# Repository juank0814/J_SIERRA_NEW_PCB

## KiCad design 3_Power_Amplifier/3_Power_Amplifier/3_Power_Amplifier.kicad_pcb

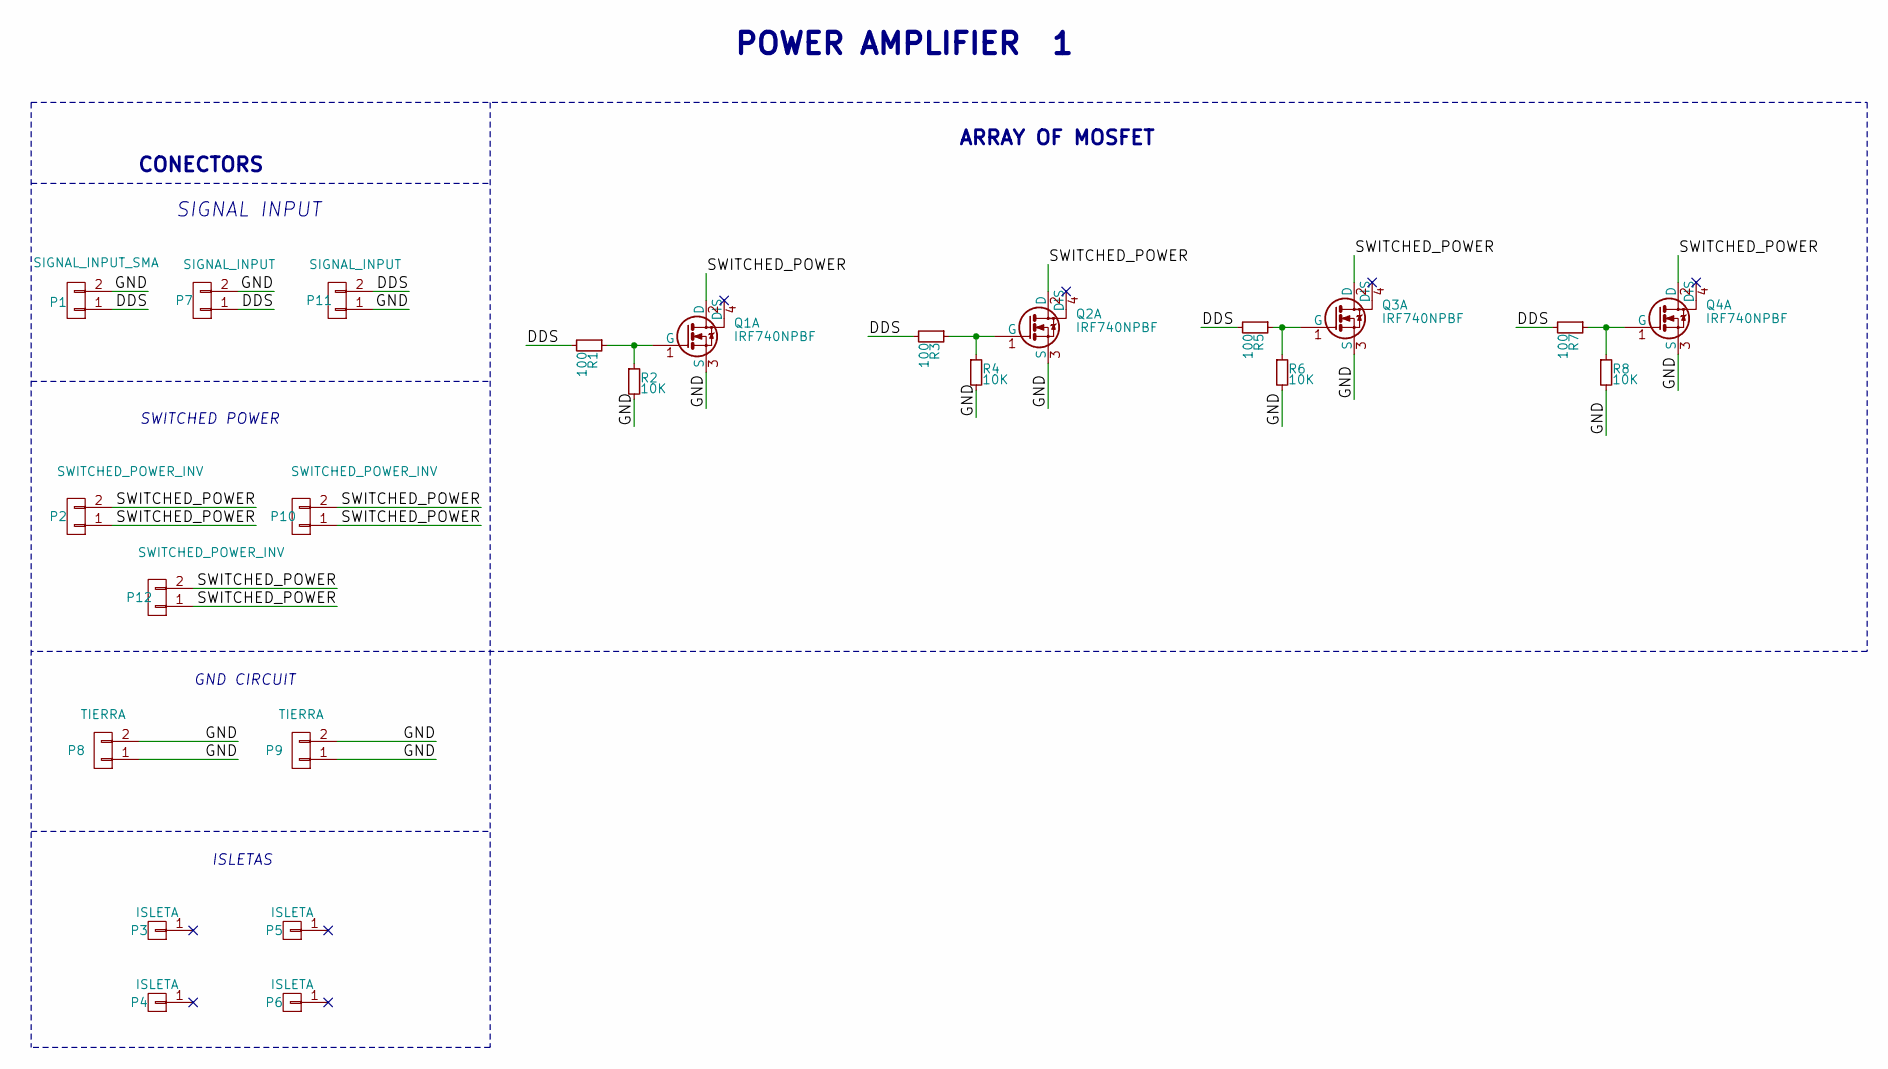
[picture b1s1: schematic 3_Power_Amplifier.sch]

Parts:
P1: SIGNAL_INPUT_SMA; INV_SMA_THT_Jack_Straight
P2, P10, P12: SWITCHED_POWER_INV; INV_Socket_MOLEX-2-pines
P3, P4, P5, P6: ISLETA; MountingHole_3.2mm_M3_Pad_Via
P7, P11: SIGNAL_INPUT; REDISEÑADO_INV_Pin_Header_Pitch2.54mm
P8, P9: TIERRA; INV_Socket_MOLEX-2-pines
Q1, Q2, Q3, Q4: IRF740NPBF; TO-220_Ver_Disipador
R1, R3, R5, R7: 100; R_0805_HandSoldering
R2, R4, R6, R8: 10K; R_0805_HandSoldering

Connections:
/DDS: P1.1, P7.1, P11.2, R1.2, R3.2, R5.2, R7.2
/GND: P1.2, P7.2, P8.1, P8.2, P9.1, P9.2, P11.1, Q1.3 (S), Q2.3 (S), Q3.3 (S), Q4.3 (S), R2.2, R4.2, R6.2, R8.2
/SWITCHED_POWER: P2.1, P2.2, P10.1, P10.2, P12.1, P12.2, Q1.2 (D), Q2.2 (D), Q3.2 (D), Q4.2 (D)
unnamed: Q1.1 (G), R1.1, R2.1
unnamed: Q2.1 (G), R3.1, R4.1
unnamed: Q3.1 (G), R5.1, R6.1
unnamed: Q4.1 (G), R7.1, R8.1

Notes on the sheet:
CONECTORS
ARRAY OF MOSFET
POWER AMPLIFIER 1
SIGNAL INPUT
SWITCHED POWER
GND CIRCUIT
ISLETAS

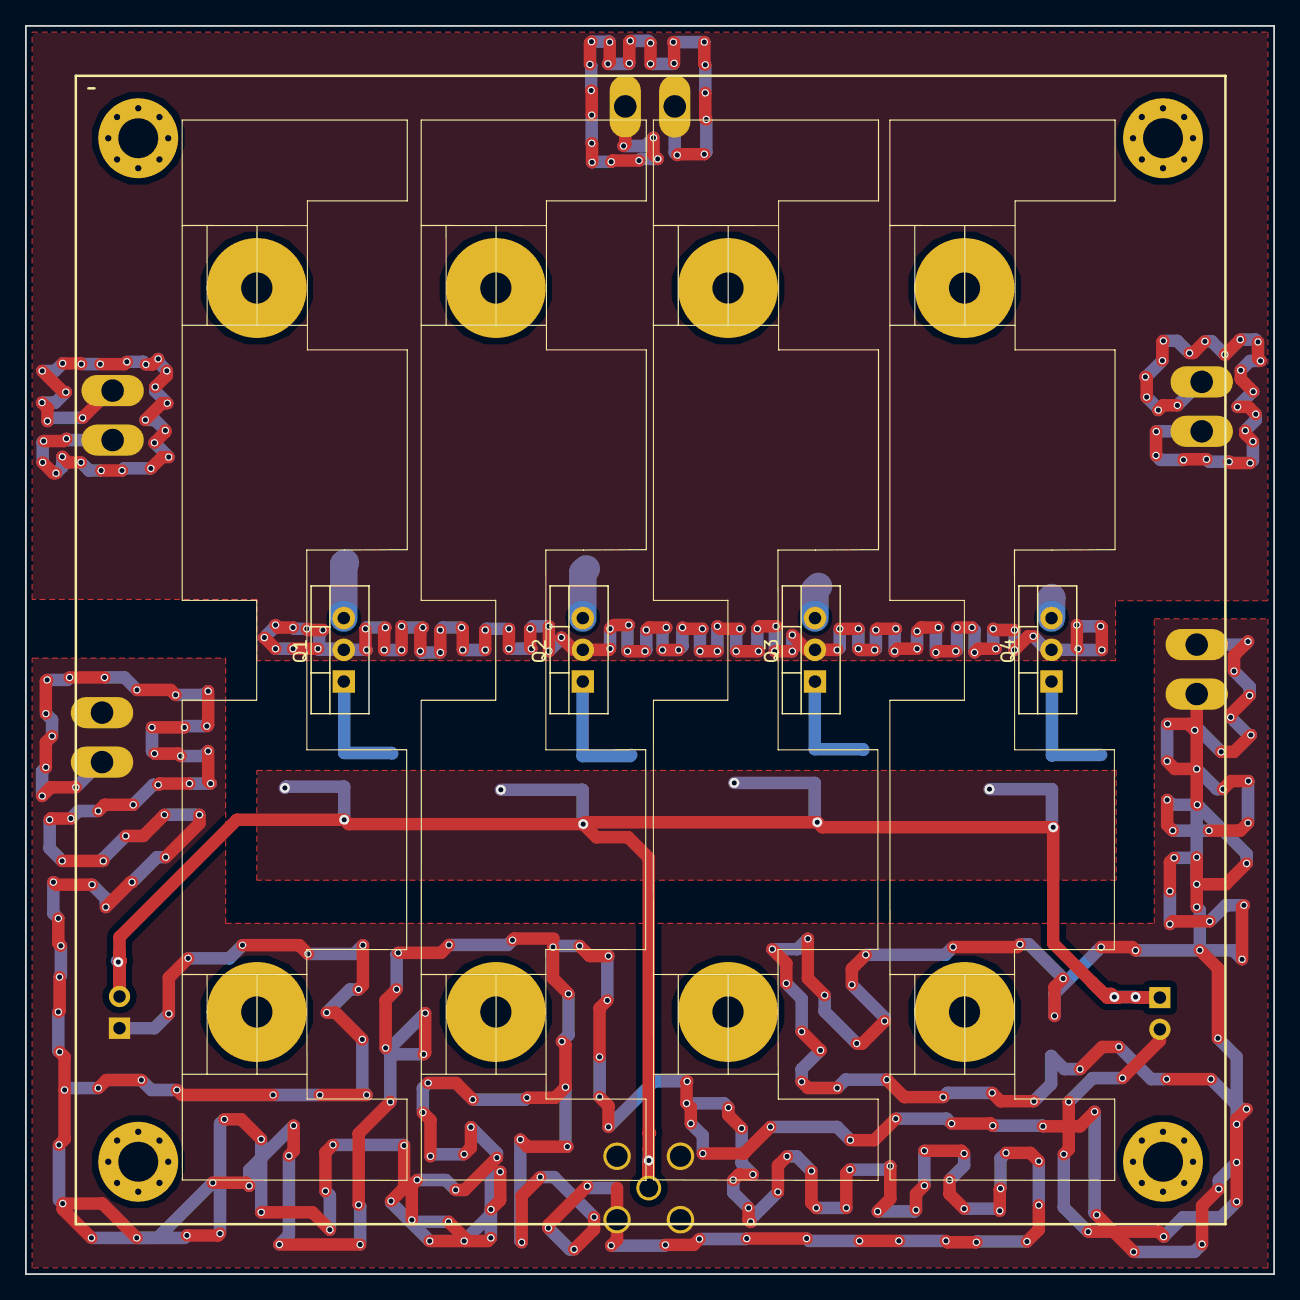
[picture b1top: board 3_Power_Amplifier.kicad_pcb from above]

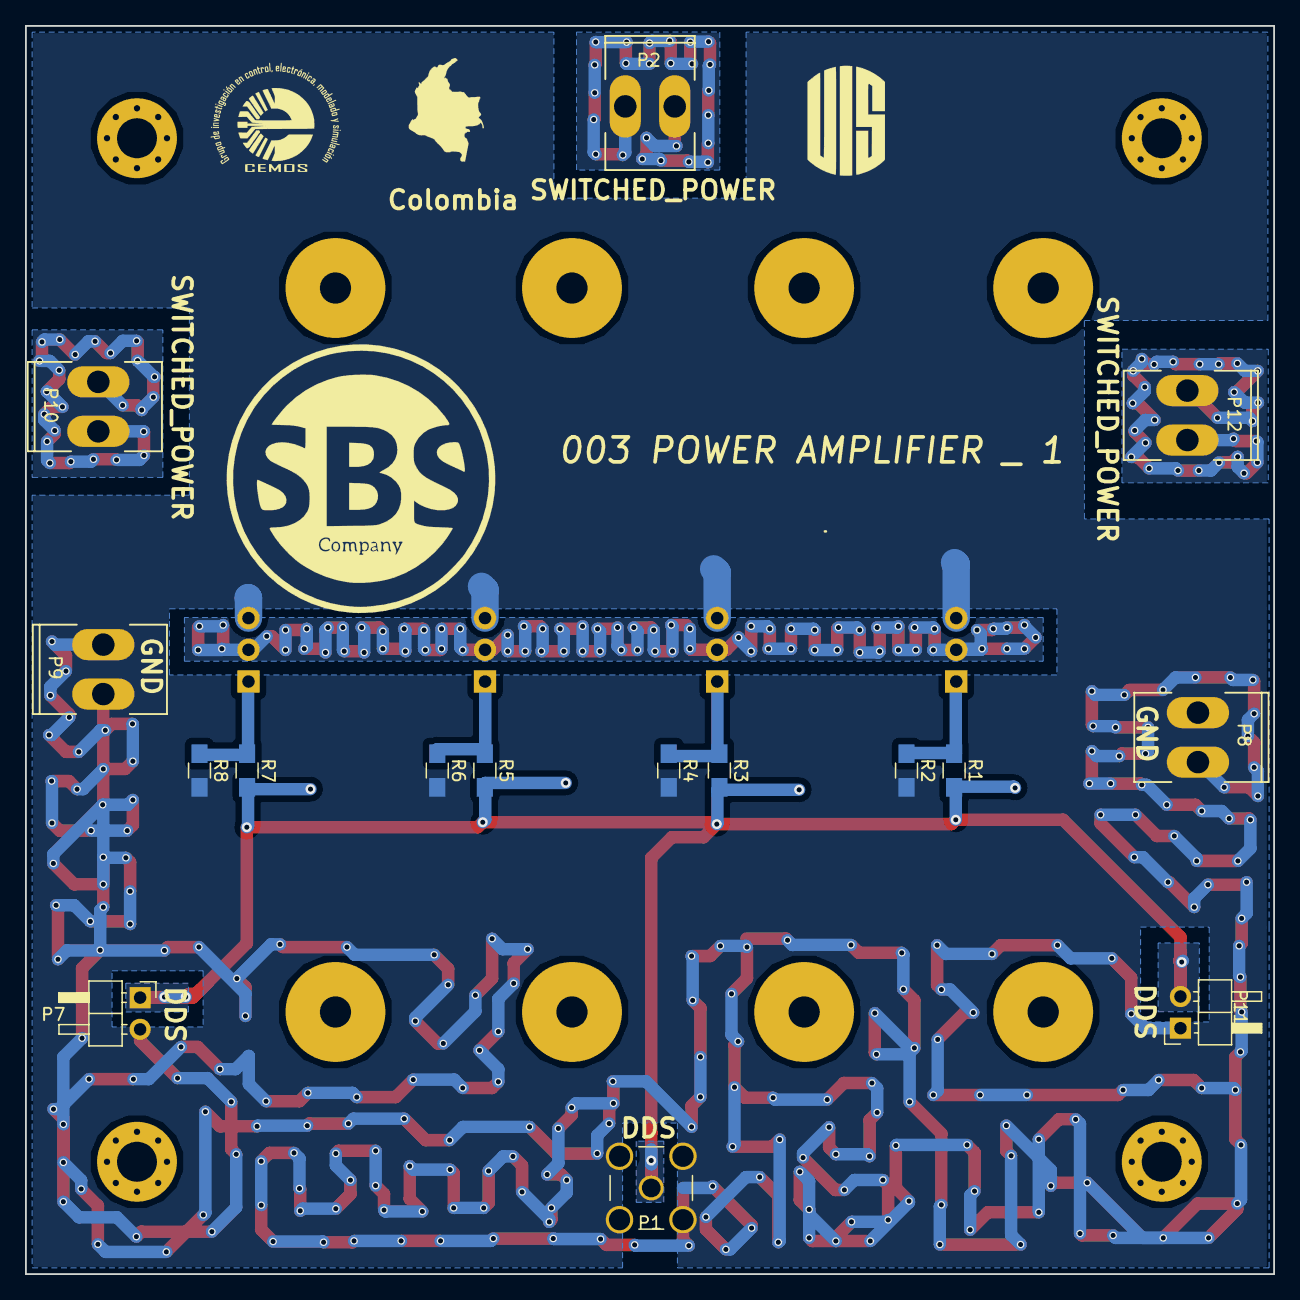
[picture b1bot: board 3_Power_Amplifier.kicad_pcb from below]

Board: 2 copper layers, 100.0 x 100.0 mm, 24 parts (8 on the bottom side), 7 nets.

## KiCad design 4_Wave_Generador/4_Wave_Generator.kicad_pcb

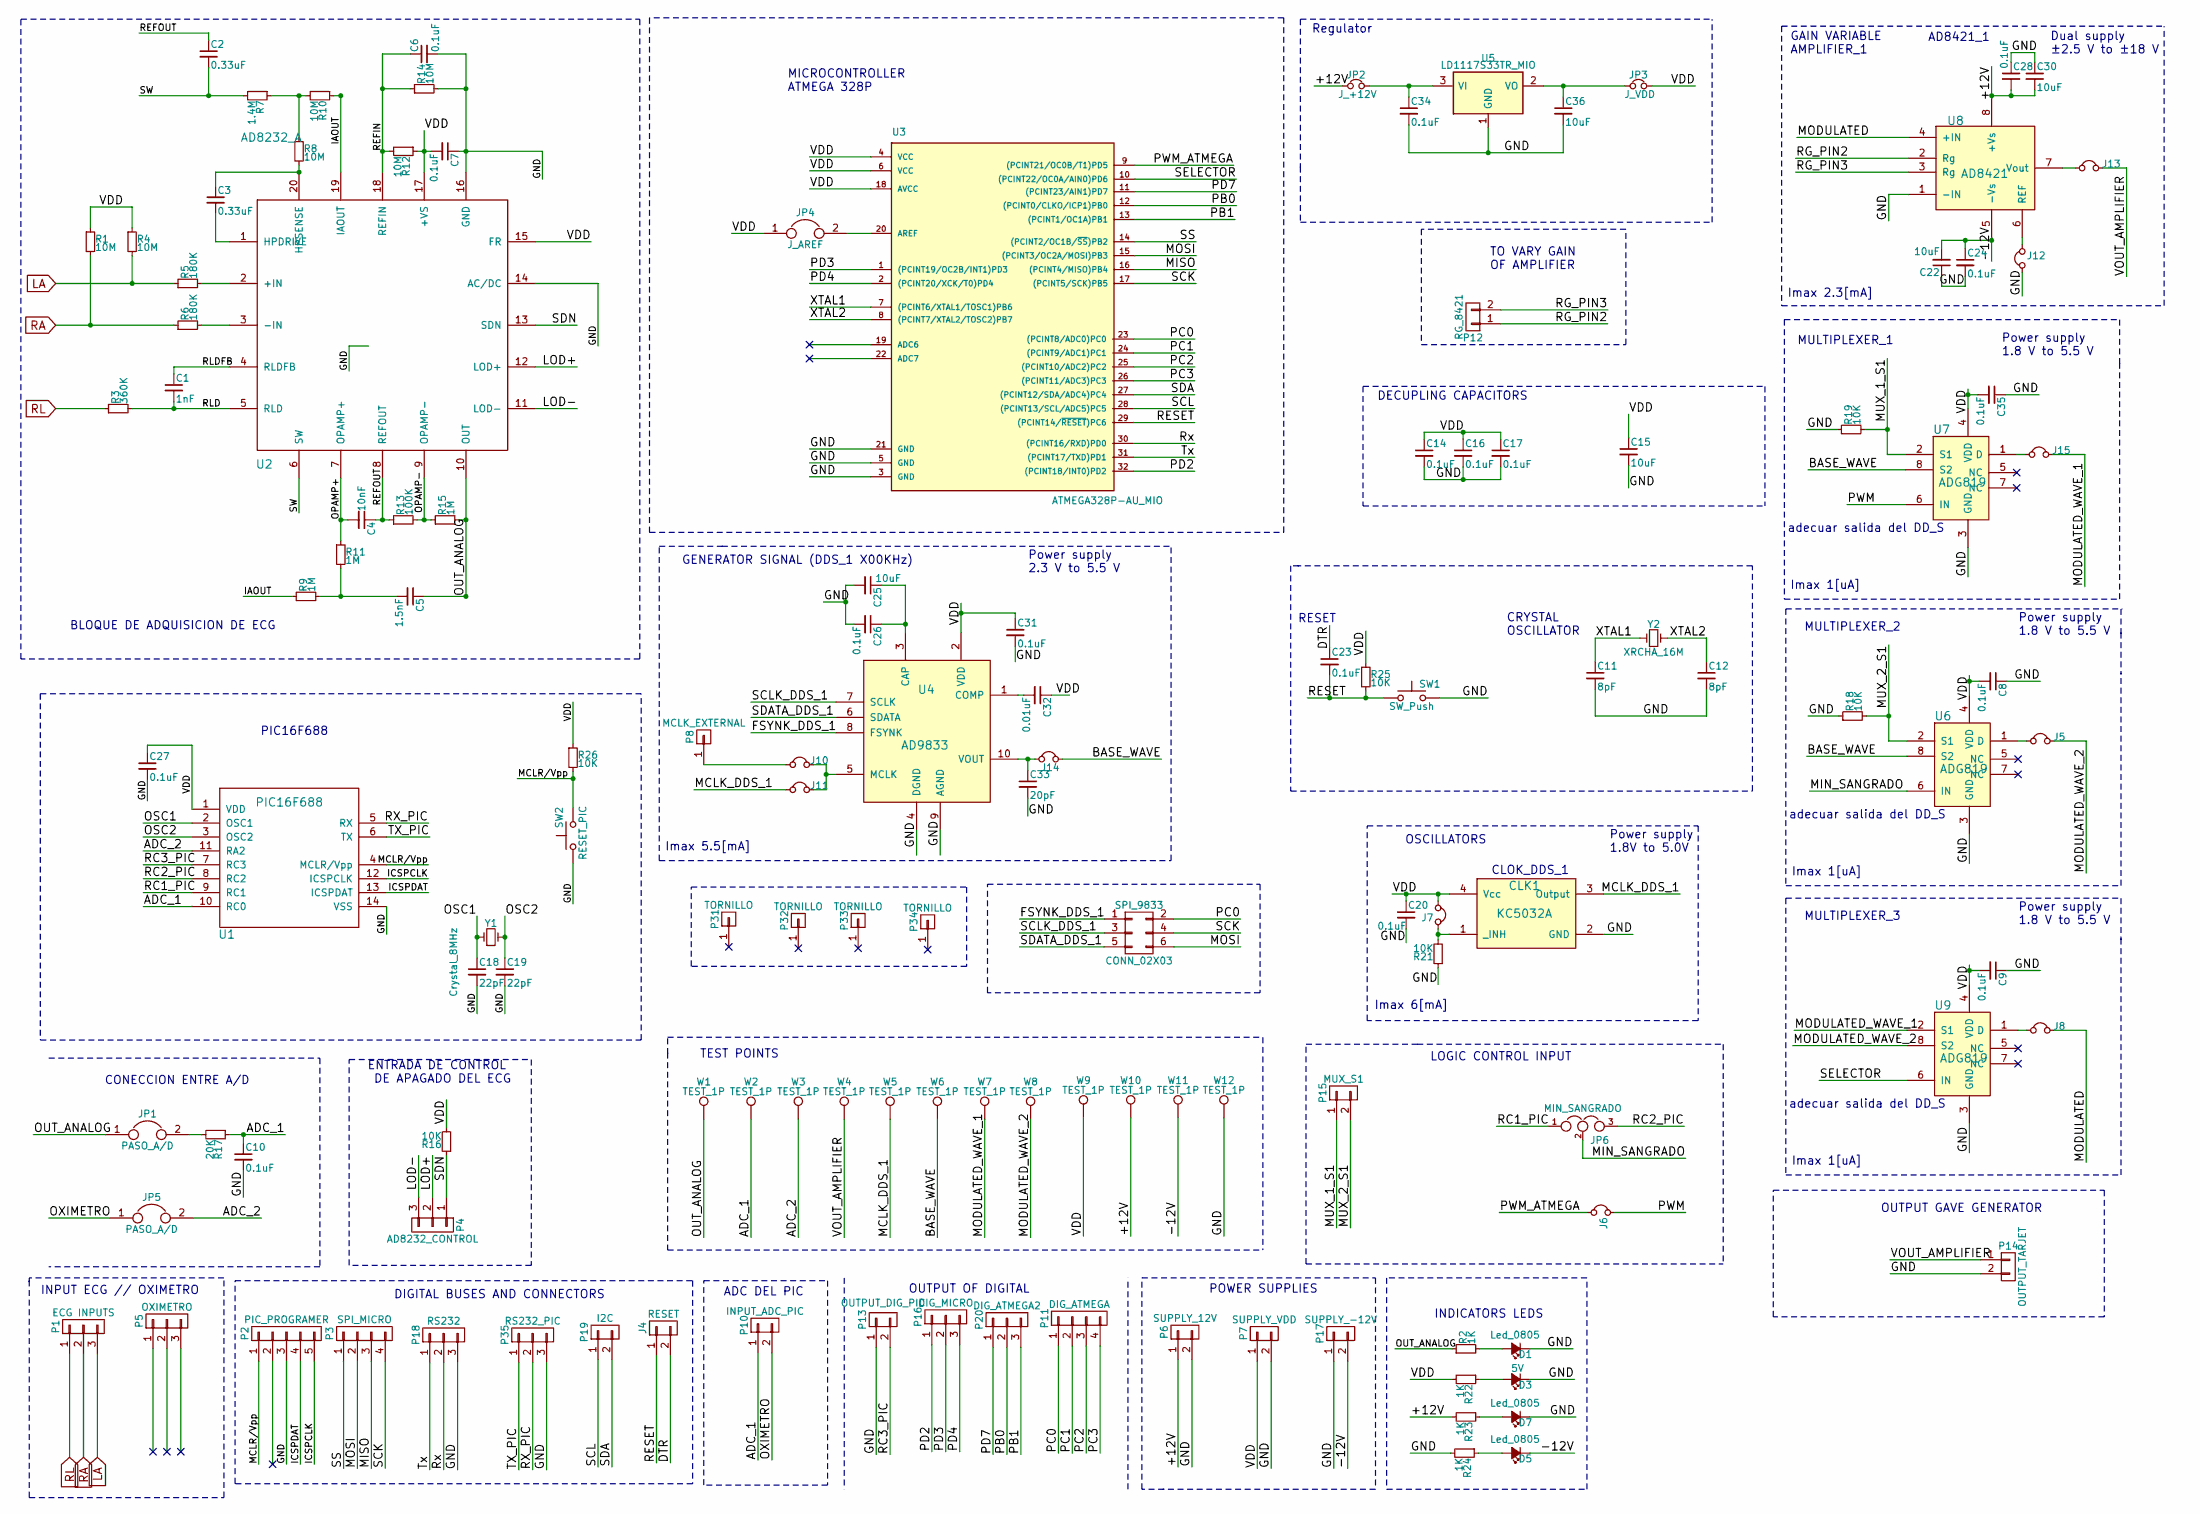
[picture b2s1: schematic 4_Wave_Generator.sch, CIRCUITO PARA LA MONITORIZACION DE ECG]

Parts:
C1: 1nF; C_0805_HandSoldering
C2, C3: 0.33uF; C_0805_HandSoldering
C4: 10nF; C_0805_HandSoldering
C5: 1.5nF; C_0805_HandSoldering
C6, C7, C10, C27: 0.1uF; C_0805_HandSoldering
C8, C9, C20, C24, C26, C28, C31, C35: 0.1uF; C_0805_HandSoldering; Digi-Key Part Number 478-1395-2-ND
C11, C12: 8pF; R_0402
C14, C16, C17, C23, C34: 0.1uF; R_0805_HandSoldering; Digi-Key Part Number 478-1395-2-ND
C15, C25: 10uF; C_0805_HandSoldering
C18, C19: 22pF; C_0805_HandSoldering
C22, C30: 10uF; C_1206_HandSoldering
C32: 0.01uF; C_0805_HandSoldering; Digi-Key Part Number 478-1383-2-ND
C33: 20pF; C_0805_HandSoldering
C36: 10uF; R_0805_HandSoldering
CLK1: KC5032A; KC5032A_Foot_Print
D1, D5, D7: Led_0805; R_0805_HandSoldering; Digi-Key Part Number 475-1410-2-ND
D3: 5V; R_0805_HandSoldering; Digi-Key Part Number 475-1410-2-ND
J4: RESET; RESET_CONNECTOR
J5, J6, J7, J8, J10, J11, J12, J13, J14, J15: Jumper; Pin_Header_Straight_1x02_Pitch2.54mm
JP1, JP5: PASO_A/D; Pin_Header_Straight_1x02_Pitch2.54mm
JP2: J_+12V; Pin_Header_Straight_1x02_Pitch2.54mm
JP3: J_VDD; Pin_Header_Straight_1x02_Pitch2.54mm
JP4: J_AREF; Pin_Header_Straight_1x02_Pitch2.54mm
JP6: MIN_SANGRADO; Pin_Header_Straight_1x03_Pitch2.54mm
P1: ECG INPUTS; Pin_Header_Straight_1x03_Pitch2.54mm
P2: PIC_PROGRAMER
P3: SPI_MICRO; SPI_CONNECTOR
P4: AD8232_CONTROL; Pin_Header_Straight_1x03_Pitch2.54mm
P5: OXIMETRO
P6: SUPPLY_12V
P7: SUPPLY_VDD; SUPPLY_5V
P8: MCLK_EXTERNAL
P10: INPUT_ADC_PIC; ADC_PIC
P11: DIG_ATMEGA; Pin_Header_Straight_1x04_Pitch2.54mm
P12: RG_8421
P13: OUTPUT_DIG_PIC; Pin_Header_Straight_1x02_Pitch2.54mm
P14: OUTPUT_TARJET; VOUT
P15: MUX_S1; Pin_Header_Straight_1x02_Pitch2.54mm
P16: DIG_MICRO; Pin_Header_Straight_1x03_Pitch2.54mm
P17: SUPPLY_-12V
P18: RS232
P19: I2C; I2C_2X4
P20: DIG_ATMEGA2; Pin_Header_Straight_1x03_Pitch2.54mm
P31, P32, P33, P34: TORNILLO; MountingHole_3.2mm_M3_Pad_Via
P35: RS232_PIC; RS232
R1, R4, R8, R10, R12, R14: 10M; R_0805_HandSoldering
R2, R22, R23, R24: 1K; R_0805_HandSoldering
R3: 360K; R_0805_HandSoldering
R5, R6: 180K; R_0805_HandSoldering
R7: 1.4M; R_0805_HandSoldering
R9, R11, R15: 1M; R_0805_HandSoldering
R13: 100K; R_0805_HandSoldering
R16, R18, R19, R21, R25, R26: 10K; R_0805_HandSoldering
R17: 20K; R_0805_HandSoldering
SPI_9833: CONN_02X03; SPI_9833
SW1: SW_Push; KPT_1187B
SW2: RESET_PIC; KPT_1187B
U1: PIC16F688; SOIC-14_3.9x8.7mm_Pitch1.27mm
U2: AD8232_A; AD8232_ECG
U3: ATMEGA328P-AU_MIO; TQFP-32_7x7mm_Pitch0.8mm
U4: AD9833; MSOP-10_3x3mm_Pitch0.5mm
U5: LD1117S33TR_MIO; SOT-223_este
U6, U7, U9: ADG819; MSOP-8_3x3mm_Pitch0.65mm
U8: AD8421; SOIC-8_3.9x4.9mm_Pitch1.27mm
W1, W2, W3, W4, W5, W6, W7, W8, W9, W10, W11, W12: TEST_1P; Measurement_Point_Round-TH_Small
Y1: Crystal_8MHz; Crystal_SMD_Abracon_ABM3-2pin_5.0x3.2mm_HandSoldering
Y2: XRCHA_16M; Crystal_SMD_XRCHA_Murata_Serie_W2,5mm_L2,0mm

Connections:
/+12V: C28.2, C30.2, JP2.1, P6.1, R23.2, U8.8 (+Vs), W10.1; also elsewhere on the board
/-12V: C22.2, C24.1, D5.1 (K), P17.2, U8.5 (-Vs), W11.1; also elsewhere on the board
/ADC_1: C10.1, P10.1, R17.1, U1.10 (RC0), W2.1
/ADC_2: JP5.2, U1.11 (RA2), W3.1
/BASE_WAVE: J14.1, U6.8 (S2), U7.8 (S2), W6.1; also elsewhere on the board
/DTR: C23.1, J4.2
/FSYNK_DDS_1: SPI_9833.1, U4.8 (FSYNK)
/GND: C6.2, C7.1, C8.1, C9.1, C10.2, C11.2, C12.2, C14.2, C15.2, C16.2, C17.2, C18.2, C19.2, C20.2, C22.1, C24.2, C25.2, C26.2, C27.2, C28.1, C30.1, C31.2, C33.2, C34.2, C35.1, C36.2, CLK1.2 (GND), D1.1 (K), D3.1 (K), D7.1 (K), J12.2, P2.3, P6.2, P7.2, P13.1, P14.2, P17.1, P18.3, P35.3, R14.2, R18.1, R19.1, R21.1, R24.2, SW1.2, SW2.1, U1.14 (VSS), U2.14 (AC/DC), U2.16 (GND), U2.21 (GND), U3.3 (GND), U3.5 (GND), U3.21 (GND), U4.4 (DGND), U4.9 (AGND), U5.1 (GND), U6.3 (GND), U7.3 (GND), U8.1 (-IN), U9.3 (GND), W12.1; also elsewhere on the board
/IAOUT: R9.1, R10.1, U2.19 (IAOUT); also elsewhere on the board
/ICSPCLK: P2.5, U1.12 (ICSPCLK)
/ICSPDAT: P2.4, U1.13 (ICSPDAT)
/LOD+: P4.2 (LA), U2.12 (LOD+); also elsewhere on the board
/LOD-: P4.3 (RA), U2.11 (LOD-); also elsewhere on the board
/MCLK_DDS_1: CLK1.3 (Output), J11.2, W5.1
/MCLR/Vpp: P2.1, R26.2, SW2.2, U1.4 (MCLR/Vpp)
/MIN_SANGRADO: JP6.2, U6.6 (IN); also elsewhere on the board
/MISO: P3.3, U3.16 ((PCINT4/MISO)PB4)
/MODULATED: J8.1, U8.4 (+IN); also elsewhere on the board
/MODULATED_WAVE_1: J15.1, U9.2 (S1), W7.1; also elsewhere on the board
/MODULATED_WAVE_2: J5.1, U9.8 (S2), W8.1; also elsewhere on the board
/MOSI: P3.2, SPI_9833.6, U3.15 ((PCINT3/OC2A/MOSI)PB3)
/MUX_1_S1: P15.1, R19.2, U7.2 (S1); also elsewhere on the board
/MUX_2_S1: P15.2, R18.2, U6.2 (S1); also elsewhere on the board
/OPAMP+: C4.2, R11.1, U2.7 (OPAMP+); also elsewhere on the board
/OSC1: C18.1, U1.2 (OSC1), Y1.1
/OSC2: C19.1, U1.3 (OSC2), Y1.2
/OUT_ANALOG: C5.1, JP1.1, R2.1, R15.2, U2.10 (OUT), W1.1; also elsewhere on the board
/OXIMETRO: JP5.1, P10.2
/PB0: P20.2, U3.12 ((PCINT0/CLKO/ICP1)PB0)
/PB1: P20.3, U3.13 ((PCINT1/OC1A)PB1)
/PC0: P11.1, SPI_9833.2, U3.23 ((PCINT8/ADC0)PC0)
/PC1: P11.2, U3.24 ((PCINT9/ADC1)PC1)
/PC2: P11.3, U3.25 ((PCINT10/ADC2)PC2)
/PC3: P11.4, U3.26 ((PCINT11/ADC3)PC3)
/PD2: P16.1, U3.32 ((PCINT18/INT0)PD2)
/PD3: P16.2, U3.1 ((PCINT19/OC2B/INT1)PD3)
/PD4: P16.3, U3.2 ((PCINT20/XCK/T0)PD4)
/PD7: P20.1, U3.11 ((PCINT23/AIN1)PD7)
/PWM: J6.1, U7.6 (IN); also elsewhere on the board
/PWM_ATMEGA: J6.2, U3.9 ((PCINT21/OC0B/T1)PD5)
/RC1_PIC: JP6.1, U1.9 (RC1)
/RC2_PIC: JP6.3, U1.8 (RC2)
/RC3_PIC: P13.2, U1.7 (RC3)
/REFIN: C6.1, R12.2, R14.1, U2.18 (REFIN); also elsewhere on the board
/REFOUT: C2.1, C4.1, R13.1, U2.8 (REFOUT); also elsewhere on the board
/RESET: C23.2, J4.1, R25.2, SW1.1, U3.29 ((PCINT14/~RESET~)PC6)
/RG_PIN2: P12.1, U8.2 (Rg); also elsewhere on the board
/RG_PIN3: P12.2, U8.3 (Rg); also elsewhere on the board
/RLD: C1.2, R3.2, U2.5 (RLD); also elsewhere on the board
/RLDFB: C1.1, U2.4 (RLDFB); also elsewhere on the board
/RX_PIC: P35.2, U1.5 (RX)
/Rx: P18.2, U3.30 ((PCINT16/RXD)PD0)
/SCK: P3.4, SPI_9833.4, U3.17 ((PCINT5/SCK)PB5)
/SCL: P19.1, U3.28 ((PCINT13/SCL/ADC5)PC5)
/SCLK_DDS_1: SPI_9833.3, U4.7 (SCLK)
/SDA: P19.2, U3.27 ((PCINT12/SDA/ADC4)PC4)
/SDATA_DDS_1: SPI_9833.5, U4.6 (SDATA)
/SDN: P4.1 (RL), R16.1, U2.13 (SDN); also elsewhere on the board
/SELECTOR: U3.10 ((PCINT22/OC0A/AIN0)PD6), U9.6 (IN); also elsewhere on the board
/SS: P3.1, U3.14 ((PCINT2/OC1B/~SS~)PB2)
/SW: C2.2, R7.2, U2.6 (SW); also elsewhere on the board
/TX_PIC: P35.1, U1.6 (TX)
/Tx: P18.1, U3.31 ((PCINT17/TXD)PD1)
/VDD: C7.2, C8.2, C9.2, C14.1, C15.1, C16.1, C17.1, C20.1, C27.1, C31.1, C32.1, C35.2, CLK1.4 (Vcc), J7.2, JP3.2, JP4.1, P7.1, R1.1, R4.1, R12.1, R16.2, R22.2, R25.1, R26.1, U1.1 (VDD), U2.15 (FR), U2.17 (+VS), U3.4 (VCC), U3.6 (VCC), U3.18 (AVCC), U4.2 (VDD), U6.4 (VDD), U7.4 (VDD), U9.4 (VDD), W9.1; also elsewhere on the board
/VOUT_AMPLIFIER: J13.1, P14.1, W4.1
/XTAL1: C11.1, U3.7 ((PCINT6/XTAL1/TOSC1)PB6), Y2.1
/XTAL2: C12.1, U3.8 ((PCINT7/XTAL2/TOSC2)PB7), Y2.2
LA: P1.3 (RA), R4.2, R5.1
unnamed 68: C3.1, R8.2, U2.20 (HPSENSE); also elsewhere on the board
unnamed 69: C3.2, U2.1 (HPDRIVE); also elsewhere on the board
unnamed: C5.2, R9.2, R11.2
unnamed: C25.1, C26.1, U4.3 (CAP)
unnamed: C32.2, U4.1 (COMP)
unnamed: C33.1, J14.2, U4.10 (VOUT)
unnamed: C34.1, JP2.2, U5.3 (VI)
unnamed: C36.1, JP3.1, U5.2 (VO)
unnamed: CLK1.1 (_INH), J7.1, R21.2
unnamed: D1.2 (A), R2.2
unnamed: D3.2 (A), R22.1
unnamed: D5.2 (A), R24.1
unnamed: D7.2 (A), R23.1
unnamed 81: J5.2, U6.1 (D); also elsewhere on the board
unnamed 82: J8.2, U9.1 (D); also elsewhere on the board
unnamed: J10.1, J11.1, U4.5 (MCLK)
unnamed 84: J10.2, P8.1; also elsewhere on the board
unnamed 85: J12.1, U8.6 (REF); also elsewhere on the board
unnamed 86: J13.2, U8.7 (Vout); also elsewhere on the board
unnamed 87: J15.2, U7.1 (D); also elsewhere on the board
unnamed: JP1.2, R17.2
unnamed: JP4.2, U3.20 (AREF)
unnamed 93: R5.2, U2.2 (+IN); also elsewhere on the board
unnamed 94: R6.2, U2.3 (-IN); also elsewhere on the board
unnamed: R7.1, R8.1, R10.2
unnamed 96: R13.2, R15.1, U2.9 (OPAMP-); also elsewhere on the board
RA: P1.2 (LA), R1.2, R6.1
RL: P1.1 (RL), R3.1

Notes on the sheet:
GENERATOR SIGNAL (DDS_1 X00KHz)
OSCILLATORS
CLOK_DDS_1
GAIN VARIABLE AMPLIFIER_1
AD8421_1
MULTIPLEXER_1
POWER SUPPLIES
Power supply 2.3 V to 5.5 V
adecuar salida del DD_S
Dual supply ±2.5 V to ±18 V
Power supply 1.8V to 5.0V
Power supply 1.8 V to 5.5 V
Imax 5.5[mA]
Imax 2.3[mA]
Imax 6[mA]
Imax 1[uA]
DIGITAL BUSES AND CONNECTORS
Regulator
RESET
CRYSTAL OSCILLATOR
DECUPLING CAPACITORS
INDICATORS LEDS
CONECCION ENTRE A/D
BLOQUE DE ADQUISICION DE ECG
ENTRADA DE CONTROL DE APAGADO DEL ECG
MULTIPLEXER_2
MICROCONTROLLER ATMEGA 328P
PIC16F688
OUTPUT OF DIGITAL
INPUT ECG // OXIMETRO
TEST POINTS
TO VARY GAIN OF AMPLIFIER
LOGIC CONTROL INPUT
OUTPUT GAVE GENERATOR
ADC DEL PIC
MULTIPLEXER_3

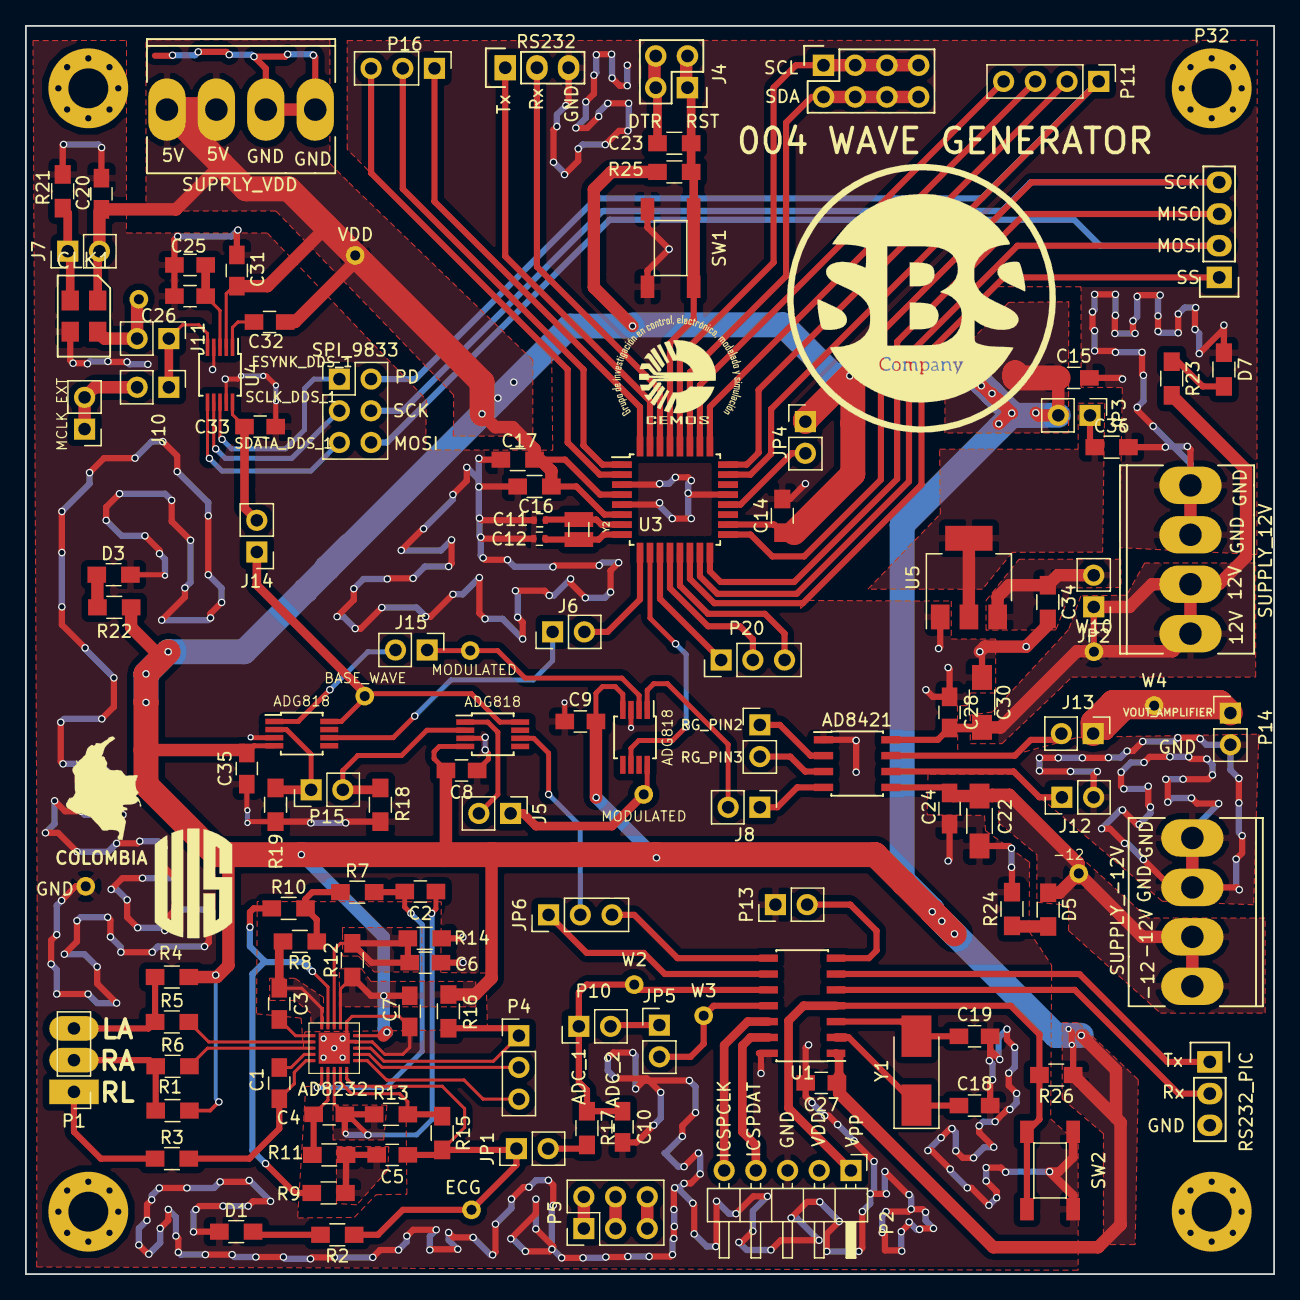
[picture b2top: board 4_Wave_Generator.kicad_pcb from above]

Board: 2 copper layers, 100.0 x 100.0 mm, 130 parts (0 on the bottom side), 96 nets.

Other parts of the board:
-12: TEST_1P; Measurement_Point_Round-TH_Small
AD8232: AD8232_A; AD8232_ECG
AD8421: AD8421; SOIC-8_3.9x4.9mm_Pitch1.27mm
ADG818, ADG818#2, ADG818#3: ADG819; MSOP-8_3x3mm_Pitch0.65mm
BASE_WAVE: TEST_1P; Measurement_Point_Round-TH_Small
ECG: TEST_1P; Measurement_Point_Round-TH_Small
GND: TEST_1P; Measurement_Point_Round-TH_Small
MCLK_EXT: MCLK_EXTERNAL
MODULATED: TEST_1P; Measurement_Point_Round-TH_Small
MODULATED#2: TEST_1P; Measurement_Point_Round-TH_Small
VDD: TEST_1P; Measurement_Point_Round-TH_Small

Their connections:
/+12V: AD8421.8; also elsewhere on the board
/-12V: -12.1, AD8421.5; also elsewhere on the board
/BASE_WAVE: ADG818.8, ADG818#2.8, BASE_WAVE.1; also elsewhere on the board
/GND: AD8232.14, AD8232.16, AD8232.21, AD8421.1, ADG818.3, ADG818#2.3, ADG818#3.3, GND.1; also elsewhere on the board
/IAOUT: AD8232.19; also elsewhere on the board
/LOD+: AD8232.12; also elsewhere on the board
/LOD-: AD8232.11; also elsewhere on the board
/MIN_SANGRADO: ADG818.6; also elsewhere on the board
/MODULATED: AD8421.4; also elsewhere on the board
/MODULATED_WAVE_1: ADG818#3.2, MODULATED.1; also elsewhere on the board
/MODULATED_WAVE_2: ADG818#3.8, MODULATED#2.1; also elsewhere on the board
/MUX_1_S1: ADG818#2.2; also elsewhere on the board
/MUX_2_S1: ADG818.2; also elsewhere on the board
/OPAMP+: AD8232.7; also elsewhere on the board
/OUT_ANALOG: AD8232.10, ECG.1; also elsewhere on the board
/PWM: ADG818#2.6; also elsewhere on the board
/REFIN: AD8232.18; also elsewhere on the board
/REFOUT: AD8232.8; also elsewhere on the board
/RG_PIN2: AD8421.2; also elsewhere on the board
/RG_PIN3: AD8421.3; also elsewhere on the board
/RLD: AD8232.5; also elsewhere on the board
/RLDFB: AD8232.4; also elsewhere on the board
/SDN: AD8232.13; also elsewhere on the board
/SELECTOR: ADG818#3.6; also elsewhere on the board
/SW: AD8232.6; also elsewhere on the board
/VDD: AD8232.15, AD8232.17, ADG818.4, ADG818#2.4, ADG818#3.4, VDD.1; also elsewhere on the board
unnamed 68: AD8232.20; also elsewhere on the board
unnamed 69: AD8232.1; also elsewhere on the board
unnamed 81: ADG818.1; also elsewhere on the board
unnamed 82: ADG818#3.1; also elsewhere on the board
unnamed 84: MCLK_EXT.1; also elsewhere on the board
unnamed 85: AD8421.6; also elsewhere on the board
unnamed 86: AD8421.7; also elsewhere on the board
unnamed 87: ADG818#2.1; also elsewhere on the board
unnamed 93: AD8232.2; also elsewhere on the board
unnamed 94: AD8232.3; also elsewhere on the board
unnamed 96: AD8232.9; also elsewhere on the board

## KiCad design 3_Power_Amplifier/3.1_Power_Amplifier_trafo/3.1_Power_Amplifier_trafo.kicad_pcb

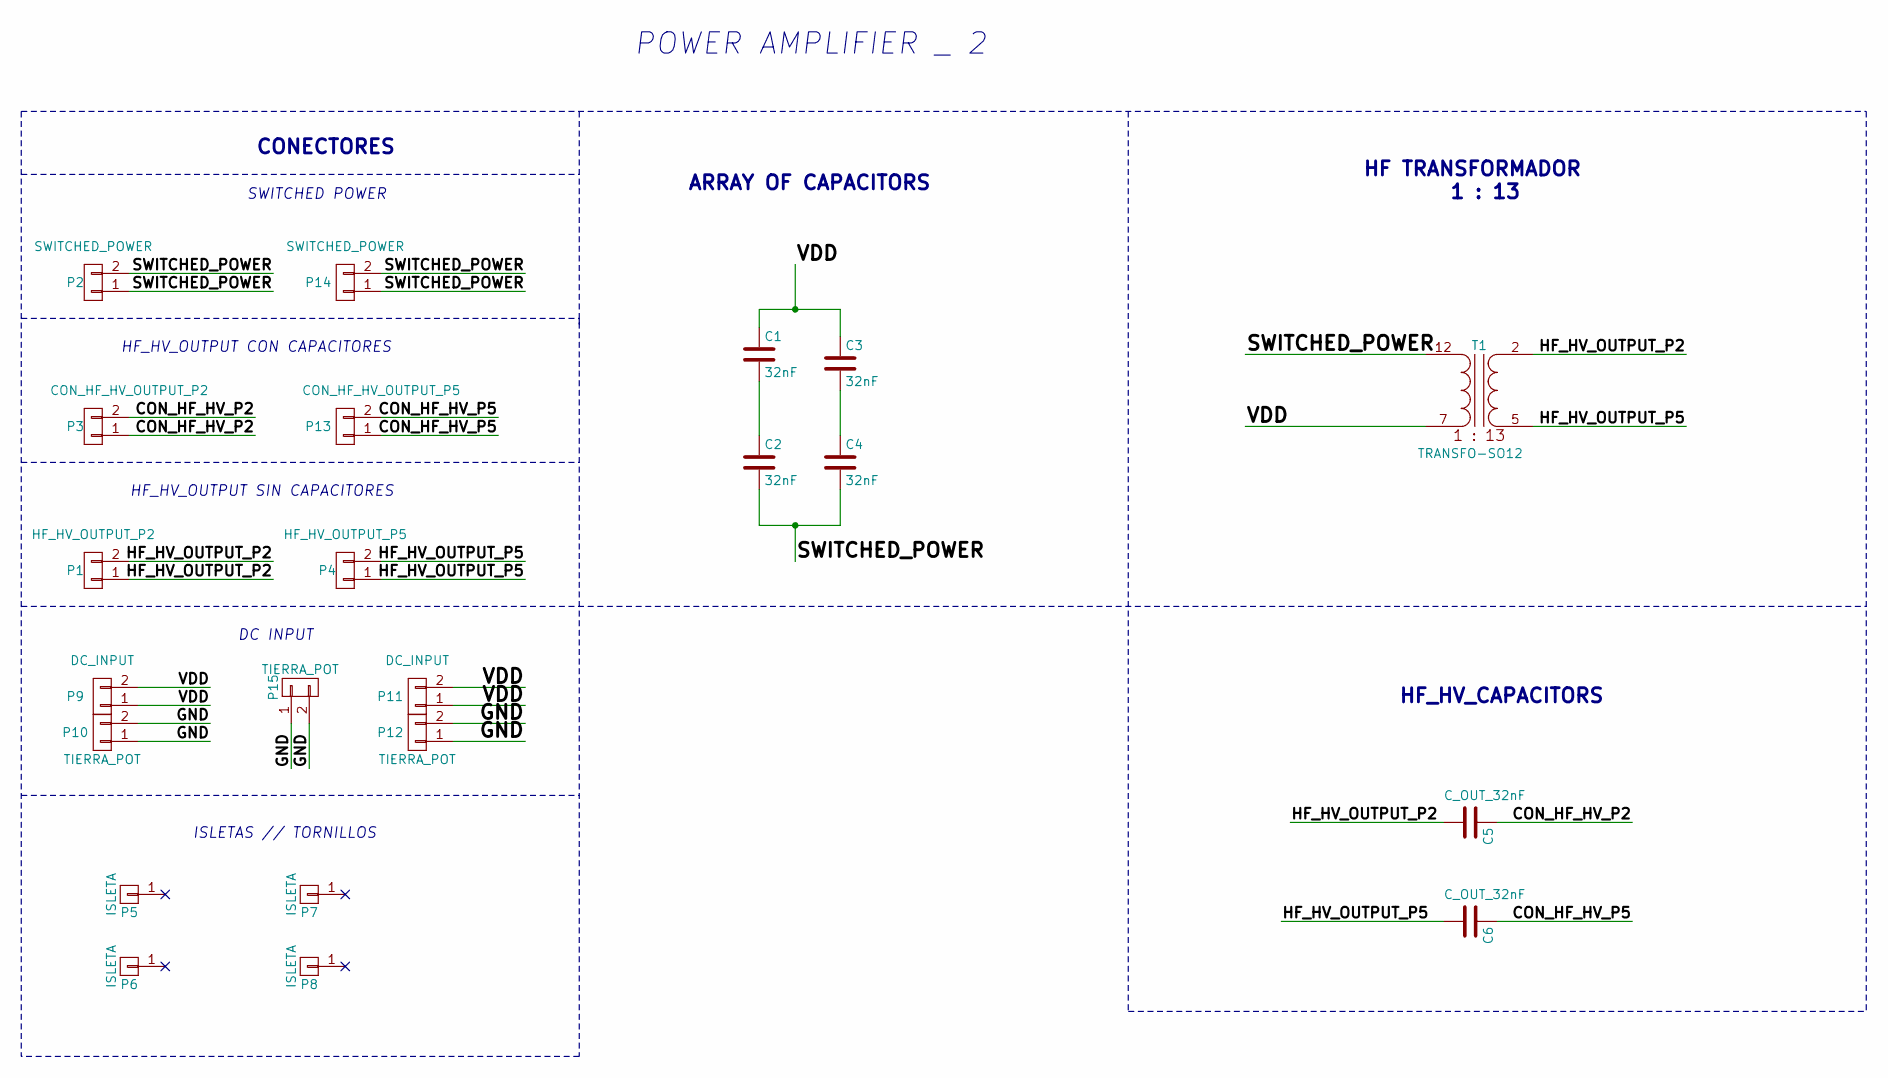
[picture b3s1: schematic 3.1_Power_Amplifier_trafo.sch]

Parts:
C1, C2, C3, C4: 32nF; C_Rect_L13.0mm_W5.0mm_P10.00mm_FKS3_FKP3_MKS4
C5, C6: C_OUT_32nF; C_Rect_L18.0mm_W7.0mm_P15.00mm_FKS3_FKP3
P1: HF_HV_OUTPUT_P2; Socket_MOLEX-KK-RM3-96mm_Lock_2pin_straight
P2, P14: SWITCHED_POWER; Socket_MOLEX-KK-RM3-96mm_Lock_2pin_straight
P3: CON_HF_HV_OUTPUT_P2; Socket_MOLEX-KK-RM3-96mm_Lock_2pin_straight
P4: HF_HV_OUTPUT_P5; Socket_MOLEX-KK-RM3-96mm_Lock_2pin_straight
P5, P6, P7, P8: ISLETA; Pad_Via_5.1mm_TOR
P9, P11: DC_INPUT; Socket_MOLEX-KK-RM3-96mm_Lock_2pin_straight
P10, P12, P15: TIERRA_POT; Socket_MOLEX-KK-RM3-96mm_Lock_2pin_straight
P13: CON_HF_HV_OUTPUT_P5; Socket_MOLEX-KK-RM3-96mm_Lock_2pin_straight
T1: TRANSFO-SO12; foot_print_trafo

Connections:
/CON_HF_HV_P2: C5.1, P3.1, P3.2
/CON_HF_HV_P5: C6.1, P13.1, P13.2
/GND: P10.1, P10.2, P12.1, P12.2, P15.1, P15.2
/HF_HV_OUTPUT_P2: C5.2, P1.1, P1.2, T1.2 (SB)
/HF_HV_OUTPUT_P5: C6.2, P4.1, P4.2, T1.5 (SA)
/SWITCHED_POWER: C2.2, C4.2, P2.1, P2.2, P14.1, P14.2, T1.12 (AA)
/VDD: C1.1, C3.1, P9.1, P9.2, P11.1, P11.2, T1.7 (AB)
unnamed: C1.2, C2.1
unnamed: C3.2, C4.1

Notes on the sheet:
CONECTORES
ARRAY OF CAPACITORS
HF TRANSFORMADOR 1 : 13
POWER AMPLIFIER _ 2
HF_HV_CAPACITORS
ISLETAS // TORNILLOS
SWITCHED POWER
HF_HV_OUTPUT CON CAPACITORES
HF_HV_OUTPUT SIN CAPACITORES
DC INPUT

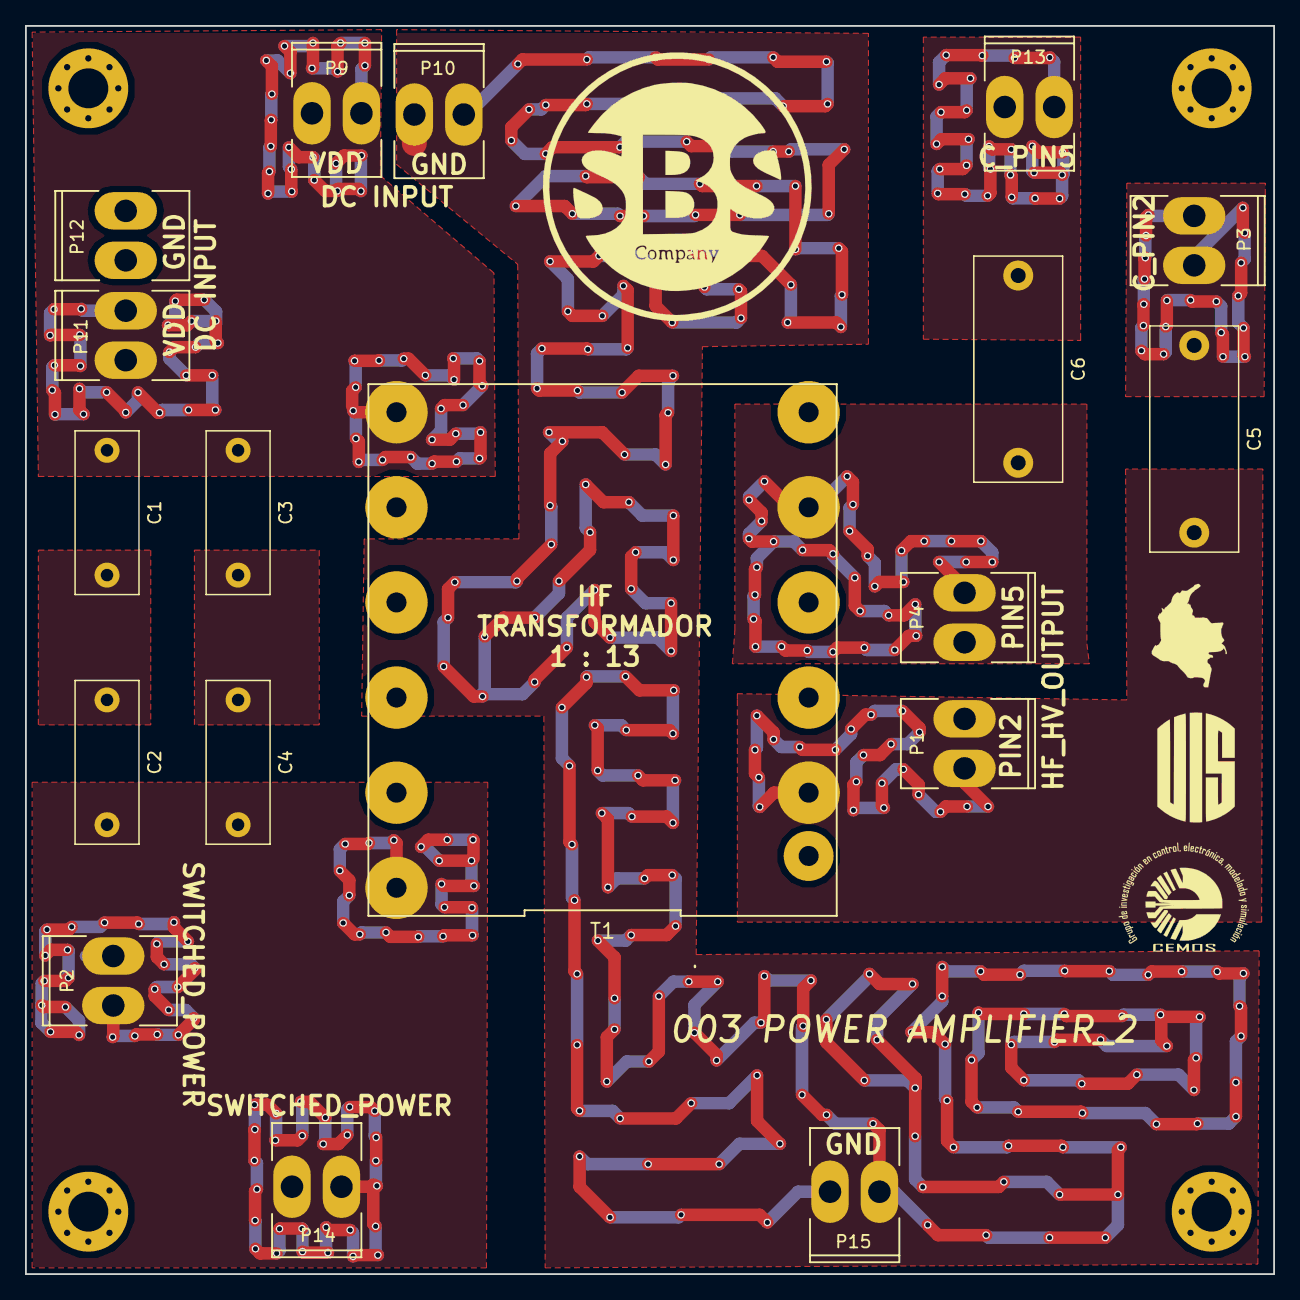
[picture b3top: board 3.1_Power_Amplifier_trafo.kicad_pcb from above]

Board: 2 copper layers, 100.0 x 100.0 mm, 22 parts (0 on the bottom side), 9 nets.
